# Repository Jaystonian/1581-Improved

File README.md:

# 1581-Improved
A similar reproduction of the 1581 for open source with improved features.

- must use a 62256 or 62c256 memory chip, the original D4364 is incompatible with this design.
- powered by 12VDC barrel connector (1 Amphere)
- please read the schematic PDF for jumper notes.

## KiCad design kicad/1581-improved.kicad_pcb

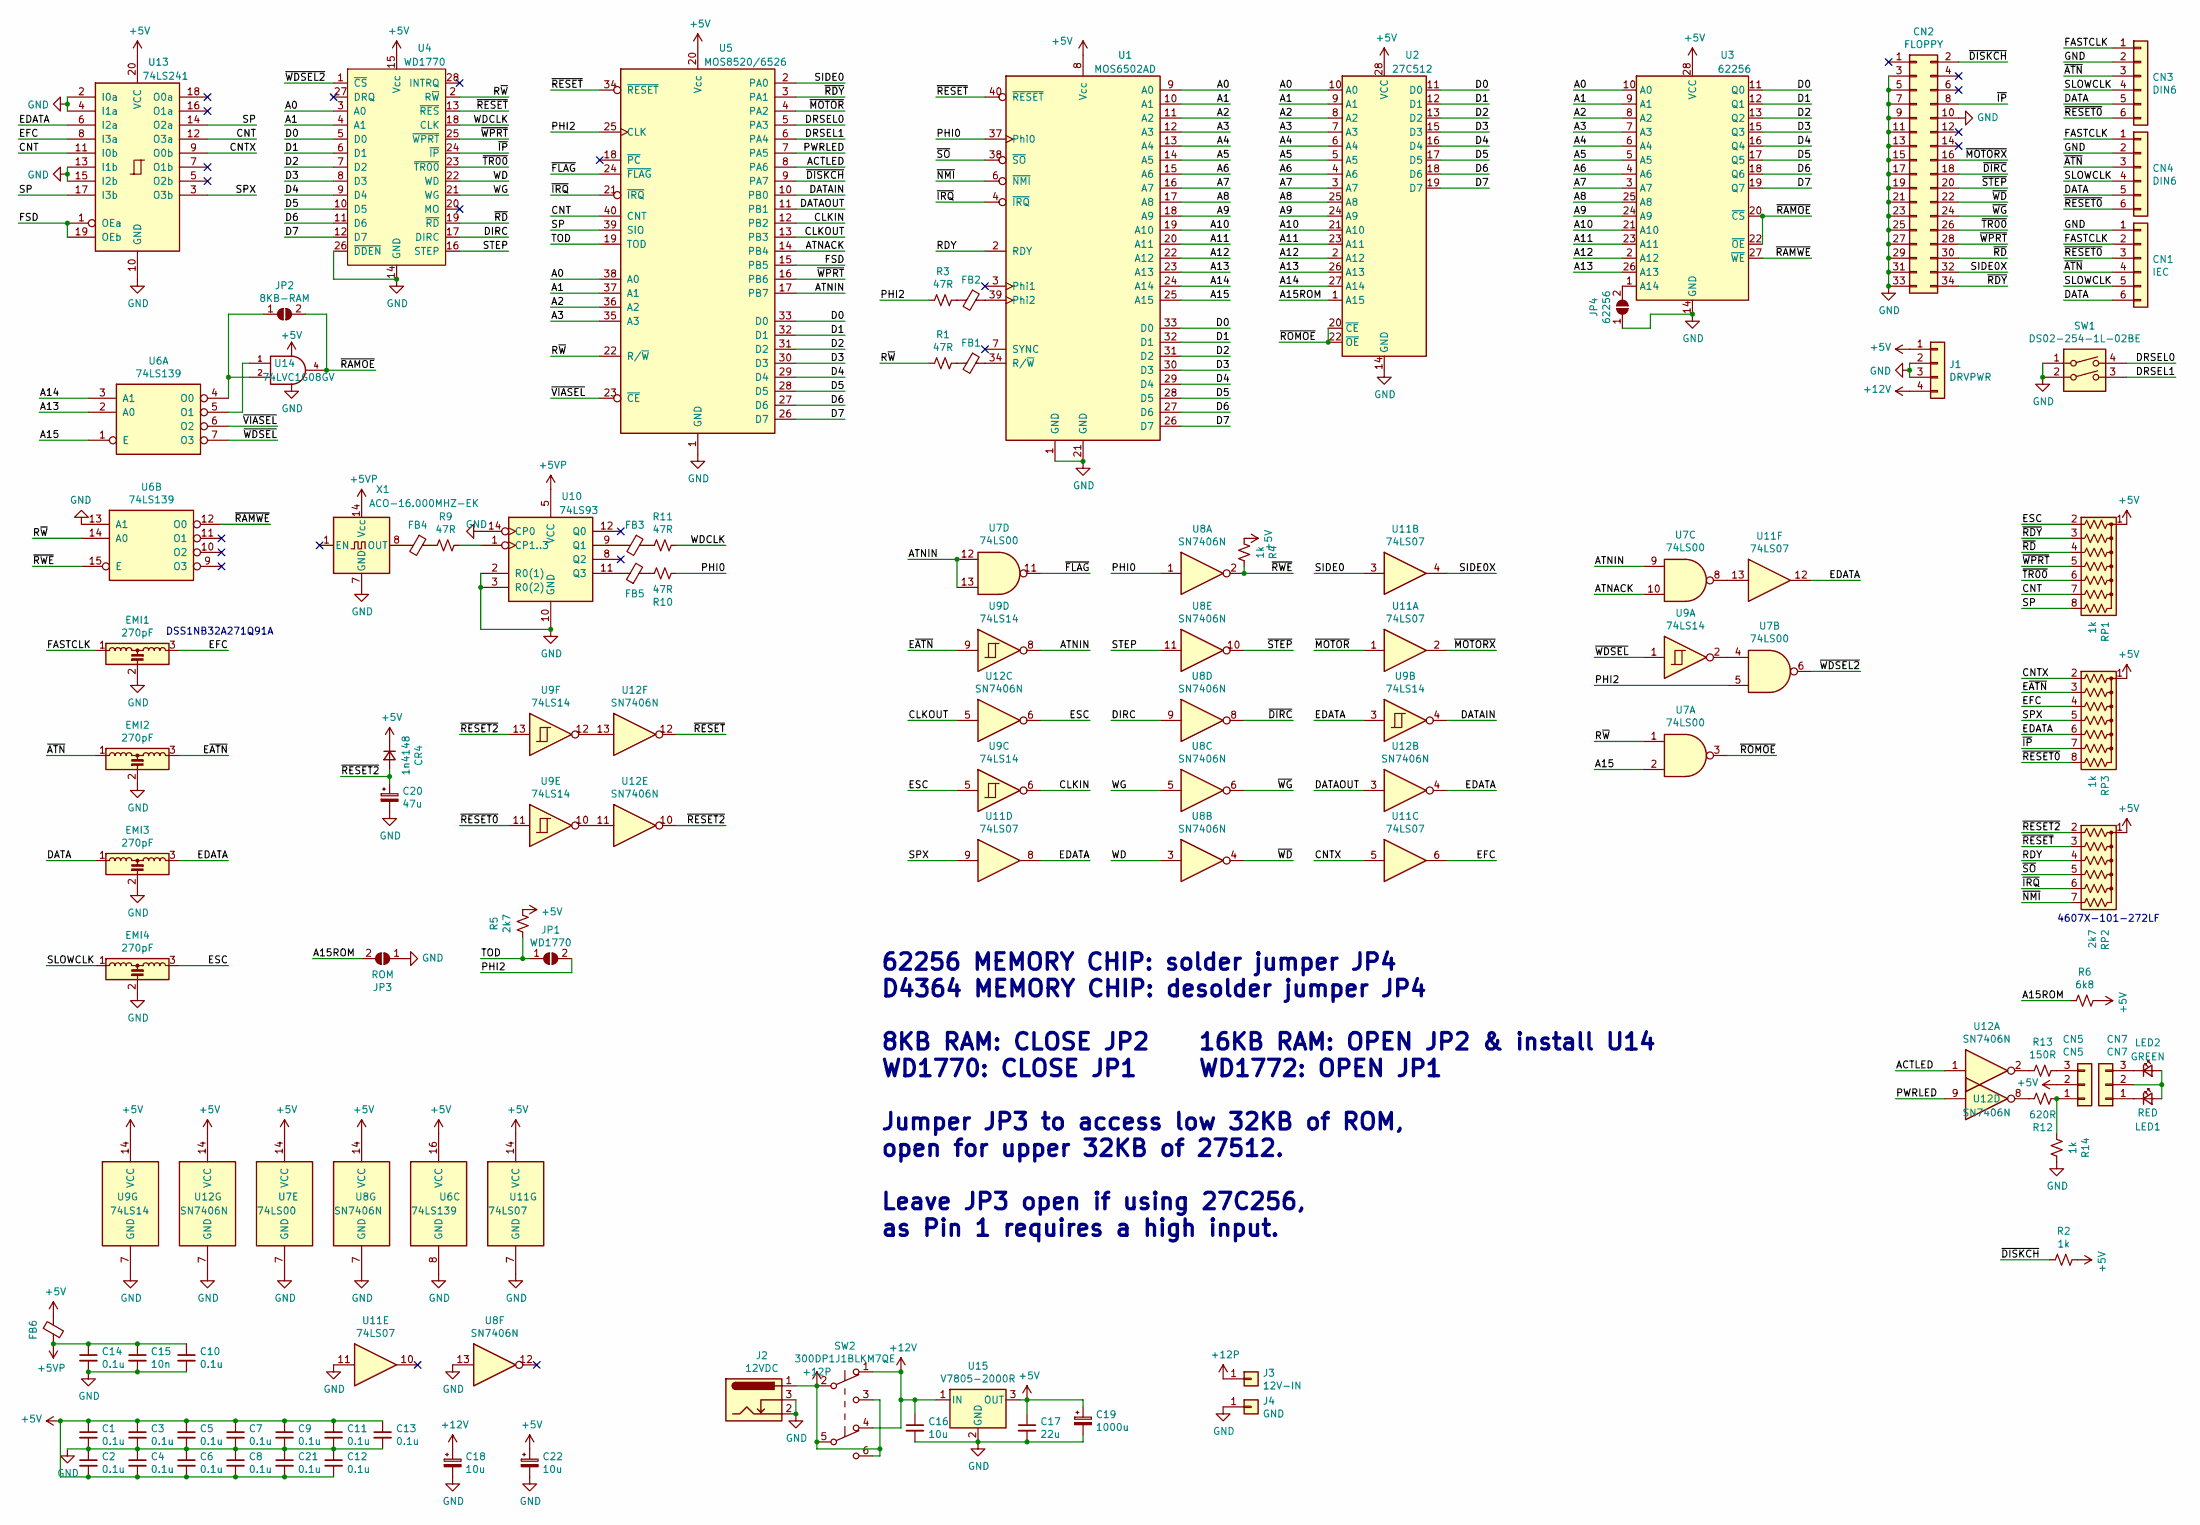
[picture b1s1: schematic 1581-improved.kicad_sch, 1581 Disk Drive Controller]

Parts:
C1, C2, C3, C4, C5, C6, C7, C8, C9, C10, C11, C12, C13, C14: 0.1u; C_Disc_D5.0mm_W2.5mm_P5.00mm
C15: 10n; C_Disc_D5.0mm_W2.5mm_P5.00mm
C16: 10u; C_0805_2012Metric_Pad1.18x1.45mm_HandSolder
C17: 22u; C_0805_2012Metric_Pad1.18x1.45mm_HandSolder
C18, C22: 10u; CP_Radial_D5.0mm_P2.50mm
C19: 1000u; CP_Axial_L25.0mm_D10.0mm_P30.00mm_Horizontal
C20: 47u; CP_Radial_D5.0mm_P2.50mm
C21: 0.1u; C_0603_1608Metric_Pad1.08x0.95mm_HandSolder
CN1: IEC; PinHeader_1x06_P2.54mm_Vertical
CN2: FLOPPY; PinHeader_2x17_P2.54mm_Vertical
CN3, CN4: DIN6; SDF-60J_DIN-6-240
CN5: CN5; PinHeader_1x03_P2.54mm_Vertical
CN7: CN7; PinHeader_1x03_P2.54mm_Vertical
CR4: 1n4148; D_DO-15_P12.70mm_Horizontal
EMI1, EMI2, EMI3, EMI4: 270pF; PinHeader_1x03_P2.54mm_Vertical
FB1, FB2, FB3, FB4, FB5, FB6: Ferrite_Bead_Small; L_Axial_L7.0mm_D3.3mm_P12.70mm_Horizontal_Fastron_MICC
J1: DRVPWR; PinHeader_1x04_P2.54mm_Vertical
J2: 12VDC; BarrelJack_Wuerth_6941xx301002
J3: 12V-IN; SolderWire-1.5sqmm_1x01_D1.7mm_OD3.9mm
J4: GND; SolderWire-1.5sqmm_1x01_D1.7mm_OD3.9mm
JP1: WD1770; SolderJumper-2_P1.3mm_Open_TrianglePad1.0x1.5mm
JP2: 8KB-RAM; SolderJumper-2_P1.3mm_Open_TrianglePad1.0x1.5mm
JP3: ROM; PinHeader_1x02_P2.54mm_Vertical
JP4: 62256; SolderJumper-2_P1.3mm_Open_TrianglePad1.0x1.5mm
LED1: RED; LED_D3.0mm
LED2: GREEN; LED_D3.0mm
R1, R3, R9, R10, R11: 47R; R_Axial_DIN0309_L9.0mm_D3.2mm_P12.70mm_Horizontal
R2, R4, R14: 1k; R_Axial_DIN0309_L9.0mm_D3.2mm_P12.70mm_Horizontal
R5: 2k7; R_Axial_DIN0309_L9.0mm_D3.2mm_P12.70mm_Horizontal
R6: 6k8; R_Axial_DIN0309_L9.0mm_D3.2mm_P12.70mm_Horizontal
R12: 620R; R_Axial_DIN0309_L9.0mm_D3.2mm_P12.70mm_Horizontal
R13: 150R; R_Axial_DIN0309_L9.0mm_D3.2mm_P12.70mm_Horizontal
RP1, RP3: 1k; R_Array_SIP8
RP2: 2k7; R_Array_SIP7
SW1: DS02-254-1L-02BE; SW_DIP_SPSTx02_Slide_9.78x7.26mm_W7.62mm_P2.54mm
SW2: 300DP1J1BLKM7QE; DPDT_1581
U1: MOS6502AD; DIP-40_W15.24mm_Socket
U2: 27C512; DIP-28_W15.24mm_Socket
U3: 62256; DIP-28_W15.24mm_Socket
U4: WD1770; DIP-28_W15.24mm_Socket
U5: MOS8520/6526; DIP-40_W15.24mm_Socket
U6: 74LS139; DIP-16_W7.62mm_Socket
U7: 74LS00; DIP-14_W7.62mm_Socket
U8, U12: SN7406N; DIP-14_W7.62mm_Socket
U9: 74LS14; DIP-14_W7.62mm_Socket
U10: 74LS93; DIP-14_W7.62mm_Socket
U11: 74LS07; DIP-14_W7.62mm_Socket
U13: 74LS241; DIP-20_W7.62mm_Socket
U14: 74LVC1G08GV; SOT-753
U15: V7805-2000R; TO-220-3_Vertical
X1: ACO-16.000MHZ-EK; Oscillator_DIP-14_LargePads

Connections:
+5V: C1.1, C2.2, C3.1, C4.2, C5.1, C6.2, C7.1, C8.2, C9.1, C11.1, C12.2, C13.1, C17.1, C19.1, C21.2, C22.1, CN5.2, CR4.1 (K), FB6.1, J1.1, R2.1, R4.2, R5.1, R6.1, RP1.1 (common), RP2.1 (common), RP3.1 (common), U1.8 (Vcc), U2.28 (VCC), U3.28 (VCC), U4.15 (Vcc), U5.20 (Vcc), U6.16 (VCC), U7.14 (VCC), U8.14 (VCC), U9.14 (VCC), U11.14 (VCC), U12.14 (VCC), U13.20 (VCC), U14.5 (VCC), U15.3 (OUT)
+5VP: C10.1, C14.1, C15.1, FB6.2, U10.5 (VCC), X1.14 (Vcc)
+12P: J2.1, J3.1, SW2.2 (B), SW2.3 (C), SW2.5 (B), SW2.6 (C)
+12V: C16.1, C18.1, J1.4, SW2.1 (A), SW2.4 (A), U15.1 (IN)
/A0: U1.9 (A0), U2.10 (A0), U3.10 (A0), U4.3 (A0), U5.38 (A0)
/A1: U1.10 (A1), U2.9 (A1), U3.9 (A1), U4.4 (A1), U5.37 (A1)
/A2: U1.11 (A2), U2.8 (A2), U3.8 (A2), U5.36 (A2)
/A3: U1.12 (A3), U2.7 (A3), U3.7 (A3), U5.35 (A3)
/A4: U1.13 (A4), U2.6 (A4), U3.6 (A4)
/A5: U1.14 (A5), U2.5 (A5), U3.5 (A5)
/A6: U1.15 (A6), U2.4 (A6), U3.4 (A6)
/A7: U1.16 (A7), U2.3 (A7), U3.3 (A7)
/A8: U1.17 (A8), U2.25 (A8), U3.25 (A8)
/A9: U1.18 (A9), U2.24 (A9), U3.24 (A9)
/A10: U1.19 (A10), U2.21 (A10), U3.21 (A10)
/A11: U1.20 (A11), U2.23 (A11), U3.23 (A11)
/A12: U1.22 (A12), U2.2 (A12), U3.2 (A12)
/A13: U1.23 (A13), U2.26 (A13), U3.26 (A13), U6.2 (A0)
/A14: U1.24 (A14), U2.27 (A14), U6.3 (A1)
/A15: U1.25 (A15), U6.1 (E), U7.2
/A15ROM: JP3.2 (B), R6.2, U2.1 (A15)
/ACTLED: U5.8 (PA6), U12.1
/ATNACK: U5.14 (PB4), U7.10
/ATNIN: U5.17 (PB7), U7.9, U7.12, U7.13, U9.8
/CLKIN: U5.12 (PB2), U9.6
/CLKOUT: U5.13 (PB3), U12.5
/CNT: RP1.7 (R6), U5.40 (CNT), U13.11 (I0b), U13.12 (O3a)
/CNTX: RP3.2 (R1), U11.5, U13.9 (O0b)
/D0: U1.33 (D0), U2.11 (D0), U3.11 (Q0), U4.5 (D0), U5.33 (D0)
/D1: U1.32 (D1), U2.12 (D1), U3.12 (Q1), U4.6 (D1), U5.32 (D1)
/D2: U1.31 (D2), U2.13 (D2), U3.13 (Q2), U4.7 (D2), U5.31 (D2)
/D3: U1.30 (D3), U2.15 (D3), U3.15 (Q3), U4.8 (D3), U5.30 (D3)
/D4: U1.29 (D4), U2.16 (D4), U3.16 (Q4), U4.9 (D4), U5.29 (D4)
/D5: U1.28 (D5), U2.17 (D5), U3.17 (Q5), U4.10 (D5), U5.28 (D5)
/D6: U1.27 (D6), U2.18 (D6), U3.18 (Q6), U4.11 (D6), U5.27 (D6)
/D7: U1.26 (D7), U2.19 (D7), U3.19 (Q7), U4.12 (D7), U5.26 (D7)
/DATA: CN1.6, CN3.5, CN4.5, EMI3.1
/DATAIN: U5.10 (PB0), U9.4
/DATAOUT: U5.11 (PB1), U12.3
/DIRC: U4.17 (DIRC), U8.9
/DRSEL0: SW1.4, U5.5 (PA3)
/DRSEL1: SW1.3, U5.6 (PA4)
/EDATA: EMI3.3, RP3.6 (R5), U9.3, U11.8, U11.12, U12.4, U13.6 (I2a)
/EFC: EMI1.3, RP3.4 (R3), U11.6, U13.8 (I3a)
/ESC: EMI4.3, RP1.2 (R1), U9.5, U12.6
/E~ATN: EMI2.3, RP3.3 (R2), U9.9
/FASTCLK: CN1.2, CN3.1, CN4.1, EMI1.1
/FSD: U5.15 (PB5), U13.1 (OEa), U13.19 (OEb)
/PHI0: R10.2, U1.37 (Phi0), U8.1
/PHI2: JP1.2 (B), R3.2, U5.25 (CLK), U7.5
/PWRLED: U5.7 (PA5), U12.9
/RDY: RP2.4 (R3), U1.2 (RDY)
/R~W: R1.2, U4.2 (R~W), U5.22 (R/~W), U6.14 (A0), U7.1
/SIDE0: U5.2 (PA0), U11.3
/SIDE0X: CN2.32, U11.4
/SLOWCLK: CN1.5, CN3.4, CN4.4, EMI4.1
/SP: RP1.8 (R7), U5.39 (SIO), U13.14 (O2a), U13.17 (I3b)
/SPX: RP3.5 (R4), U11.9, U13.3 (O3b)
/STEP: U4.16 (STEP), U8.11
/TOD: JP1.1 (A), R5.2, U5.19 (TOD)
/WD: U4.22 (WD), U8.3
/WDCLK: R11.1, U4.18 (CLK)
/WG: U4.21 (WG), U8.5
/~ATN: CN1.4, CN3.3, CN4.3, EMI2.1
/~DIRC: CN2.18, U8.8
/~DISKCH: CN2.2, R2.2, U5.9 (PA7)
/~FLAG: U5.24 (~FLAG), U7.11
/~IP: CN2.8, RP3.7 (R6), U4.24 (~IP)
/~IRQ: RP2.6 (R5), U1.4 (~IRQ), U5.21 (~IRQ)
/~MOTORX: CN2.16, U11.2
/~MOTOR: U5.4 (PA2), U11.1
/~NMI: RP2.7 (R6), U1.6 (~NMI)
/~RAMOE: JP2.2 (B), U3.20 (~CS), U3.22 (~OE), U14.4
/~RAMWE: U3.27 (~WE), U6.12 (O0)
/~RDY: CN2.34, RP1.3 (R2), U5.3 (PA1)
/~RD: CN2.30, RP1.4 (R3), U4.19 (~RD)
/~RESET0: CN1.3, CN3.6, CN4.6, RP3.8 (R7), U9.11
/~RESET2: C20.1, CR4.2 (A), RP2.2 (R1), U9.13, U12.10
/~RESET: RP2.3 (R2), U1.40 (~RESET), U4.13 (~RES), U5.34 (~RESET), U12.12
/~ROMOE: U2.20 (~CE), U2.22 (~OE), U7.3
/~RWE: R4.1, U6.15 (E), U8.2
/~SO: RP2.5 (R4), U1.38 (~SO)
/~STEP: CN2.20, U8.10
/~TR00: CN2.26, RP1.6 (R5), U4.23 (~TR00)
/~VIASEL: U5.23 (~CE), U6.6 (O2)
/~WDSEL2: U4.1 (~CS), U7.6
/~WDSEL: U6.7 (O3), U9.1
/~WD: CN2.22, U8.4
/~WG: CN2.24, U8.6
/~WPRT: CN2.28, RP1.5 (R4), U4.25 (~WPRT), U5.16 (PB6)
GND: C1.2, C2.1, C3.2, C4.1, C5.2, C6.1, C7.2, C8.1, C9.2, C10.2, C11.2, C12.1, C13.2, C14.2, C15.2, C16.2, C17.2, C18.2, C19.2, C20.2, C21.1, C22.2, CN1.1, CN2.3, CN2.5, CN2.7, CN2.9, CN2.10, CN2.11, CN2.13, CN2.15, CN2.17, CN2.19, CN2.21, CN2.23, CN2.25, CN2.27, CN2.29, CN2.31, CN2.33, CN3.2, CN4.2, EMI1.2, EMI2.2, EMI3.2, EMI4.2, J1.2, J1.3, J2.2, J2.3, J4.1, JP3.1 (A), JP4.1 (A), R14.1, SW1.1, SW1.2, U1.1 (GND), U1.21 (GND), U2.14 (GND), U3.14 (GND), U4.14 (GND), U4.26 (~DDEN), U5.1 (GND), U6.8 (GND), U6.13 (A1), U7.7 (GND), U8.7 (GND), U8.13, U9.7 (GND), U10.2 (R0(1)), U10.3 (R0(2)), U10.10 (GND), U10.14 (CP0), U11.7 (GND), U11.11, U12.7 (GND), U13.2 (I0a), U13.4 (I1a), U13.10 (GND), U13.13 (I1b), U13.15 (I2b), U14.3 (GND), U15.2 (GND), X1.7 (GND)
unnamed: CN5.1, R12.2, R14.2
unnamed: CN5.3, R13.1
unnamed: CN7.1, LED1.1 (K)
unnamed: CN7.2, LED1.2 (A), LED2.2 (A)
unnamed: CN7.3, LED2.1 (K)
unnamed: FB1.1, U1.34 (R/~W)
unnamed: FB1.2, R1.1
unnamed: FB2.1, U1.39 (Phi2)
unnamed: FB2.2, R3.1
unnamed: FB3.1, R11.2
unnamed: FB3.2, U10.9 (Q1)
unnamed: FB4.1, R9.2
unnamed: FB4.2, X1.8 (OUT)
unnamed: FB5.1, U10.11 (Q3)
unnamed: FB5.2, R10.1
unnamed: JP2.1 (A), U6.4 (O0), U14.2
unnamed: JP4.2 (B), U3.1 (A14)
unnamed: R9.1, U10.1 (CP1..3)
unnamed: R12.1, U12.8
unnamed: R13.2, U12.2
unnamed: U7.4, U9.2
unnamed: U7.8, U11.13
unnamed: U9.10, U12.11
unnamed: U9.12, U12.13
unnamed: U6.5 (O1), U14.1

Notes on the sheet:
4607X-101-272LF
DSS1NB32A271Q91A
62256 MEMORY CHIP: solder jumper JP4 D4364 MEMORY CHIP: desolder jumper JP4 8KB RAM: CLOSE JP2 16KB RAM: OPEN JP2 & install U14 WD1770: CLOSE JP1 WD1772: OPEN JP1 Jumper JP3 to access low 32KB of ROM, open for upper 32KB of 27512. Leave JP3 open if using 27C256, as Pin 1 requires a high input.

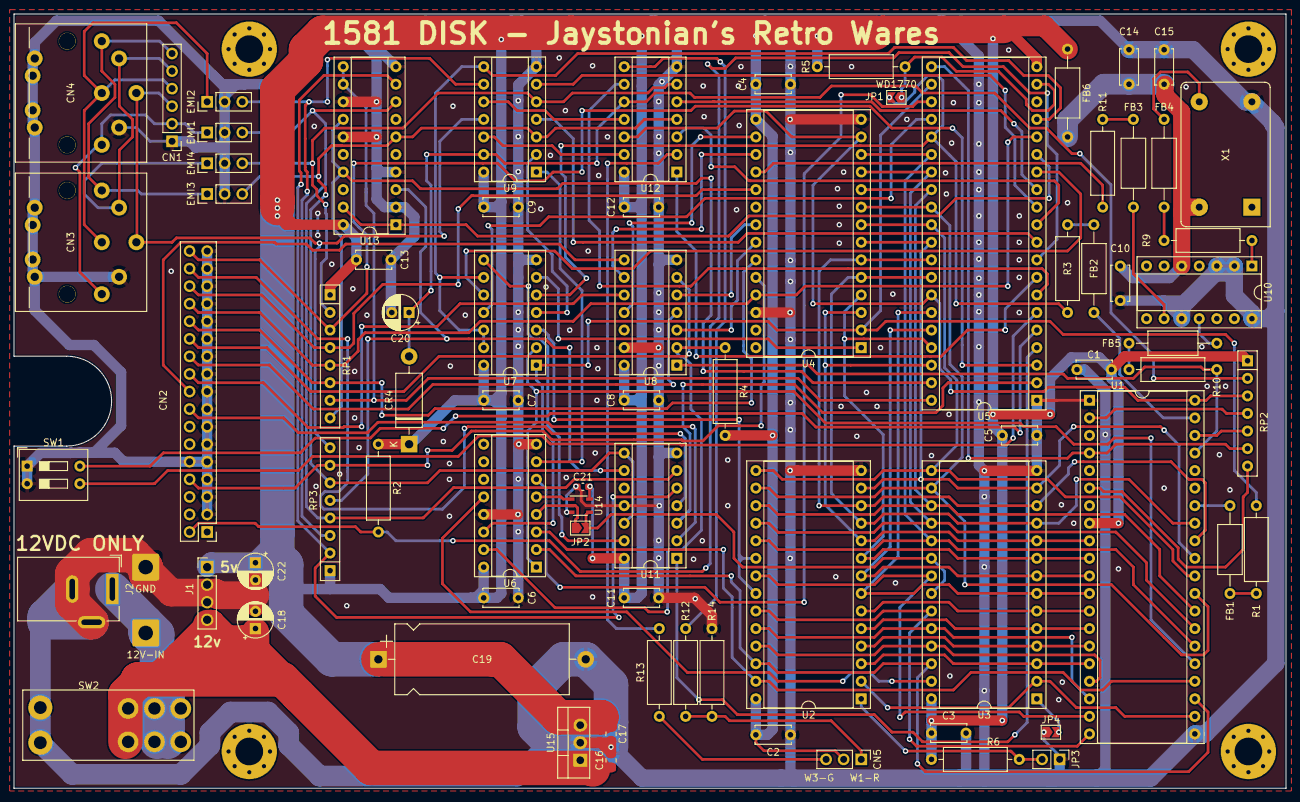
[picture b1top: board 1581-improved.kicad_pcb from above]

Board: 2 copper layers, 184.0 x 112.0 mm, 79 parts (0 on the bottom side), 113 nets.

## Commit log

2025-04-10 Small change to reduce upper lip thickness
2025-04-11 Typo on 6520 -> 8520/6526
2025-04-13 Moved the LED mount 1.5mm
2025-04-21 overhauled the face and mounts
